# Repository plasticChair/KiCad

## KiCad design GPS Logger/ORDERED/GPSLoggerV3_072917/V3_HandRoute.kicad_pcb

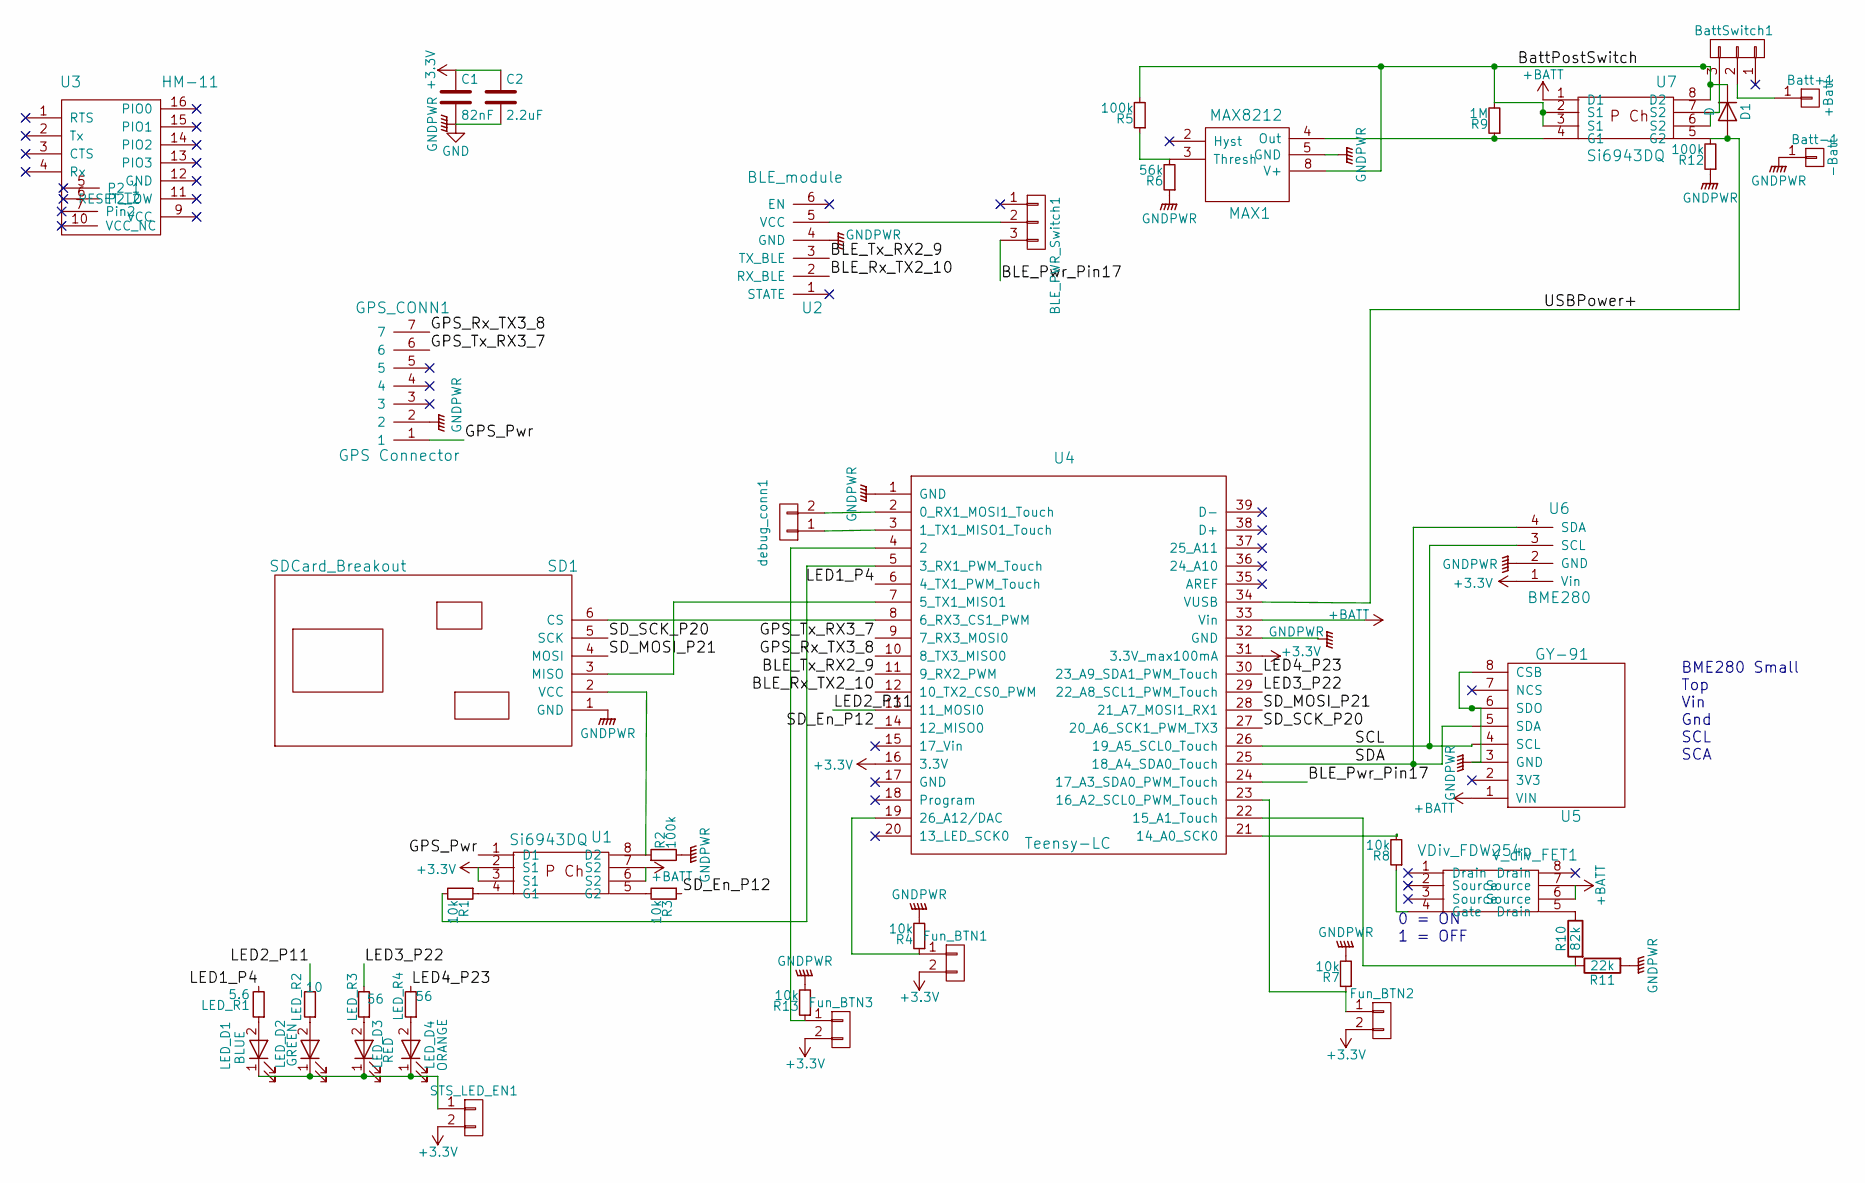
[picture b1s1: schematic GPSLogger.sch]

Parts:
BLE_PWR_Switch1: BLE_PWR_Switch; Pin_Header_1x03_Pitch2.54mm
Batt+1: +Batt; Pin_Header_1x01_Pitch2.54mm
Batt-1: -Batt; Pin_Header_1x01_Pitch2.54mm
BattSwitch1: BattSwitch; Pin_Header_1x03_Pitch2.54mm
C1: 82nF; C_0805_HandSoldering
C2: 2.2uF; C_0805_HandSoldering
D1: D; D_SOD-323
Fun_BTN1, Fun_BTN3: LVCutoff_reset; SMD_Switch_3x6
Fun_BTN2: Fun_BTN; SMD_Switch_3x6
GPS_CONN1: GPS Connector; Pin_Header_Angled_1x07_Pitch2.54mm
LED_D1: BLUE; LED_0805
LED_D2: GREEN; LED_0805
LED_D3: RED; LED_0805
LED_D4: ORANGE; LED_0805
LED_R1: 5.6; R_0805_HandSoldering
LED_R2: 10; R_0805_HandSoldering
LED_R3, LED_R4: 56; R_0805_HandSoldering
MAX1: MAX8212; SOIC-8-N
R1, R3, R4, R7, R8, R13: 10k; R_0805_HandSoldering
R2, R5, R12: 100k; R_0805_HandSoldering
R6: 56k; R_0805_HandSoldering
R9: 1M; R_0805_HandSoldering
R10: 82k; R_0805_HandSoldering
R11: 22k; R_0805_HandSoldering
SD1: SDCard_Breakout
STS_LED_EN1: STS_LED_EN; SMD_Switch_3x6
U1, U7: Si6943DQ; TSSOP-8_4.4x3mm_Pitch0.65mm_custom
U2: BLE_module; HM-10_breakout
U3: HM-11; HM-11_Breakout
U4: Teensy-LC; Teensy_LC
U5: GY-91
U6: BME280; BME280_tiny
V_div_FET1: VDiv_FDW254p; TSSOP-8_4.4x3mm_Pitch0.65mm_custom
debug_conn1: debug_conn; Pin_Header_Angled_1x02_Pitch2.54mm

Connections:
+3V3: C1.1, C2.1, Fun_BTN1.2, Fun_BTN2.2, Fun_BTN3.2, STS_LED_EN1.2, U1.2 (S1), U1.3 (S1), U4.16 (3.3V), U4.31 (3.3V_max100mA), U6.1 (Vin)
+BATT: U1.6 (S2), U1.7 (S2), U4.33 (Vin), U5.1 (VIN), U7.1 (D1), V_div_FET1.6 (Source), V_div_FET1.7 (Source)
/BLE_Pwr_Pin17: BLE_PWR_Switch1.3, U4.24 (17_A3_SDA0_PWM_Touch)
/BLE_Rx_TX2_10: U2.2 (RX_BLE), U4.12 (10_TX2_CS0_PWM)
/BLE_Tx_RX2_9: U2.3 (TX_BLE), U4.11 (9_RX2_PWM)
/BattPostSwitch: D1.1 (K), MAX1.8 (V+), R5.2, R9.2, U7.2 (S1), U7.3 (S1), U7.8 (D2)
/GPS_Pwr: GPS_CONN1.1, U1.1 (D1)
/GPS_Rx_TX3_8: GPS_CONN1.7, U4.10 (8_TX3_MISO0)
/GPS_Tx_RX3_7: GPS_CONN1.6, U4.9 (7_RX3_MOSI0)
/LED1_P4: LED_R1.2, U4.6 (4_TX1_PWM_Touch)
/LED2_P11: LED_R2.2, U4.13 (11_MOSI0)
/LED3_P22: LED_R3.2, U4.29 (22_A8_SCL1_PWM_Touch)
/LED4_P23: LED_R4.2, U4.30 (23_A9_SDA1_PWM_Touch)
/SCL: U4.26 (19_A5_SCL0_Touch), U5.4 (SCL), U6.3 (SCL)
/SDA: U4.25 (18_A4_SDA0_Touch), U5.5 (SDA), U6.4 (SDA)
/SD_En_P12: R3.1, U4.14 (12_MISO0)
/SD_MOSI_P21: SD1.4 (MOSI), U4.28 (21_A7_MOSI1_RX1)
/SD_SCK_P20: SD1.5 (SCK), U4.27 (20_A6_SCK1_PWM_TX3)
/USBPower+: D1.2 (A), R12.2, U4.34 (VUSB), U7.5 (G2)
GND: Batt-1.1, C1.2, C2.2, GPS_CONN1.2, MAX1.5 (GND), R2.2, R4.2, R6.1, R7.2, R11.2, R12.1, R13.2, SD1.1 (GND), U2.4 (GND), U4.1 (GND), U4.32 (GND), U5.3 (GND), U5.6 (SDO), U5.8 (CSB), U6.2 (GND)
unnamed: BLE_PWR_Switch1.2, U2.5 (VCC)
unnamed: Batt+1.1, BattSwitch1.2
unnamed: BattSwitch1.3, U7.6 (S2), U7.7 (S2)
unnamed: Fun_BTN1.1, R4.1, U4.19 (26_A12/DAC)
unnamed: Fun_BTN2.1, R7.1, U4.23 (16_A2_SCL0_PWM_Touch)
unnamed: Fun_BTN3.1, R13.1, U4.4 (2)
unnamed: LED_D1.1 (K), LED_D2.1 (K), LED_D3.1 (K), LED_D4.1 (K), STS_LED_EN1.1
unnamed: LED_D1.2 (A), LED_R1.1
unnamed: LED_D2.2 (A), LED_R2.1
unnamed: LED_D3.2 (A), LED_R3.1
unnamed: LED_D4.2 (A), LED_R4.1
unnamed: MAX1.3 (Thresh), R5.1, R6.2
unnamed: MAX1.4 (Out), R9.1, U7.4 (G1)
unnamed: R1.1, U1.4 (G1)
unnamed: R1.2, U4.5 (3_RX1_PWM_Touch)
unnamed: R2.1, SD1.2 (VCC), U1.8 (D2)
unnamed: R3.2, U1.5 (G2)
unnamed: R8.1, V_div_FET1.4 (Gate)
unnamed: R8.2, U4.21 (14_A0_SCK0)
unnamed: R10.1, V_div_FET1.5 (Drain)
unnamed: R10.2, R11.1, U4.22 (15_A1_Touch)
unnamed: SD1.3 (MISO), U4.7 (5_TX1_MISO1)
unnamed: SD1.6 (CS), U4.8 (6_RX3_CS1_PWM)
unnamed: U4.2 (0_RX1_MOSI1_Touch), debug_conn1.2
unnamed: U4.3 (1_TX1_MISO1_Touch), debug_conn1.1

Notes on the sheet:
0 = ON 1 = OFF
BME280 Small Top Vin Gnd SCL SCA

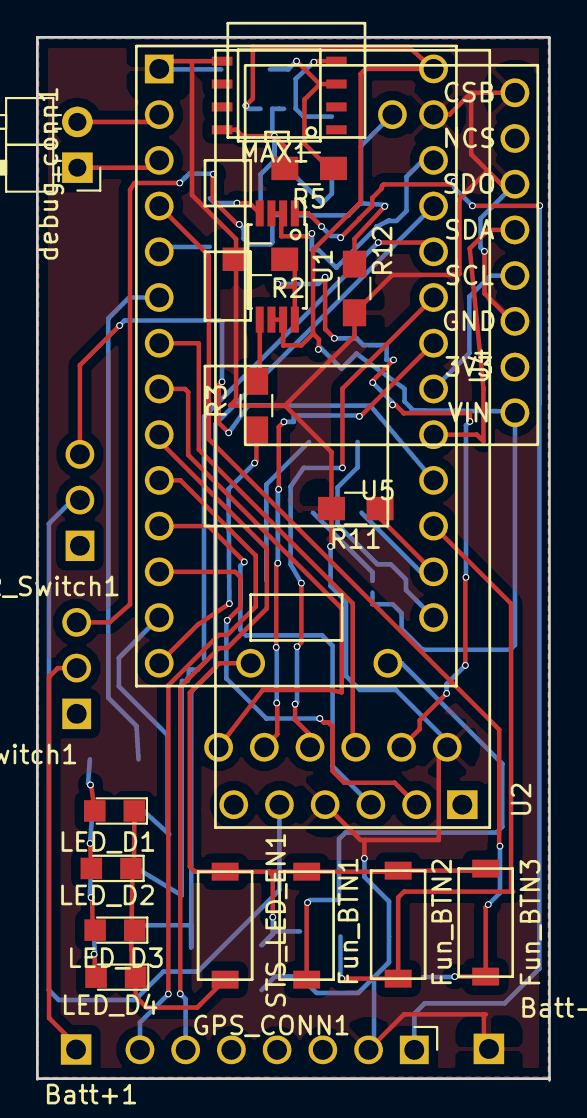
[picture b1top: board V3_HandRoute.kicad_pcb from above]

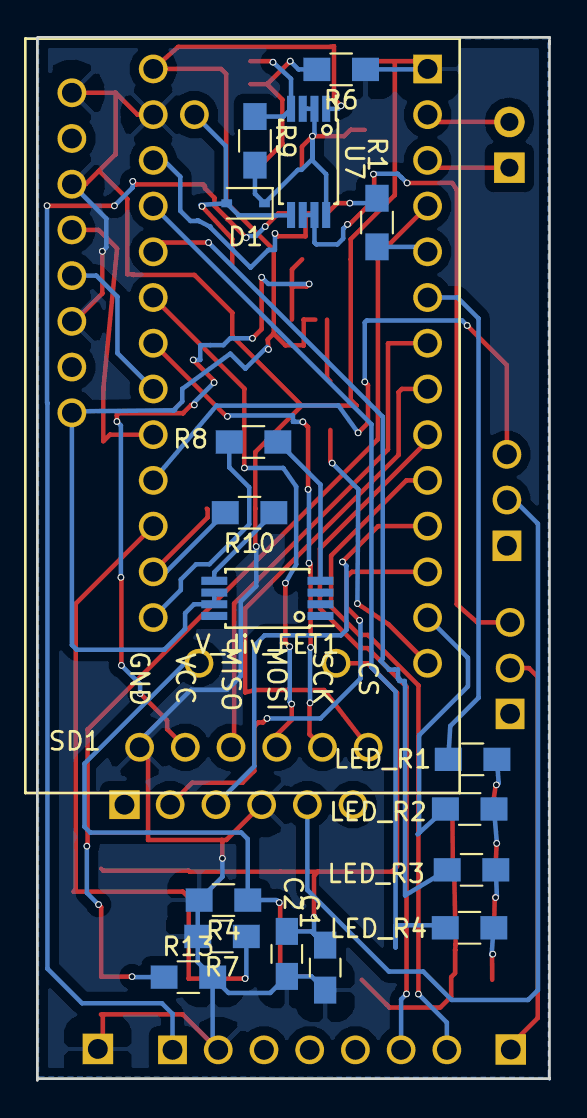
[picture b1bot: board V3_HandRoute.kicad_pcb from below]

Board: 2 copper layers, 28.4 x 58.0 mm, 42 parts (18 on the bottom side), 45 nets.

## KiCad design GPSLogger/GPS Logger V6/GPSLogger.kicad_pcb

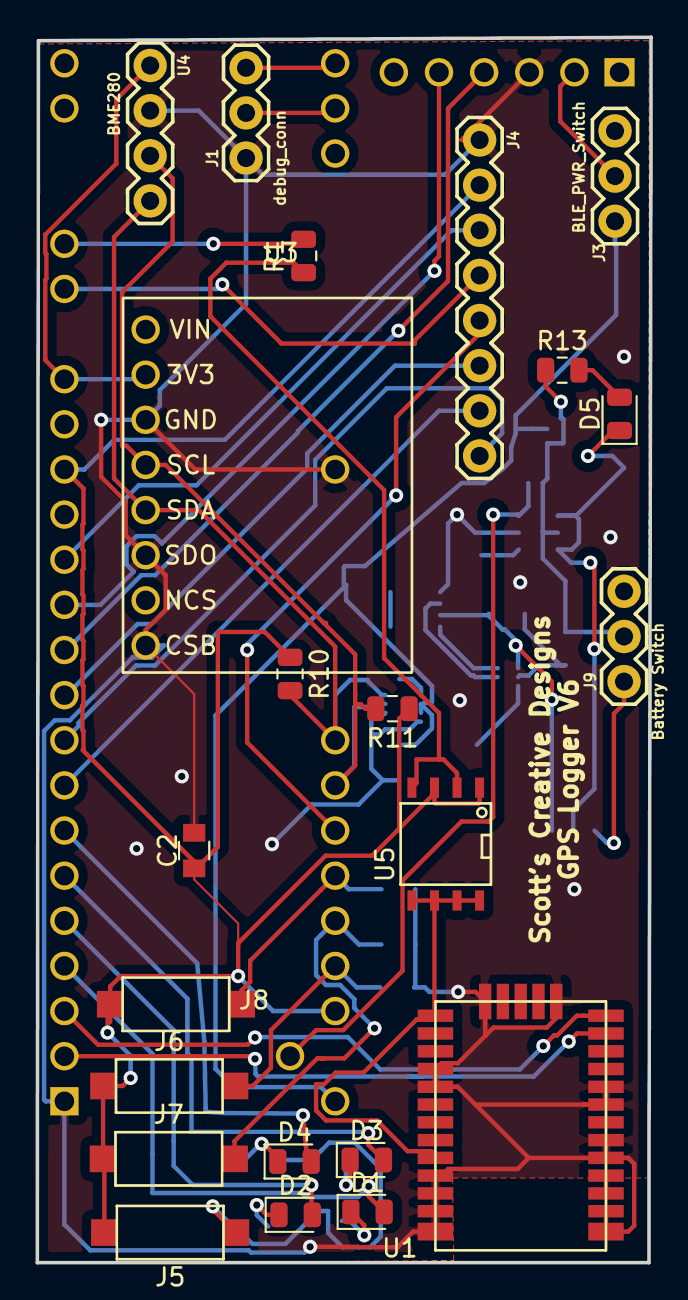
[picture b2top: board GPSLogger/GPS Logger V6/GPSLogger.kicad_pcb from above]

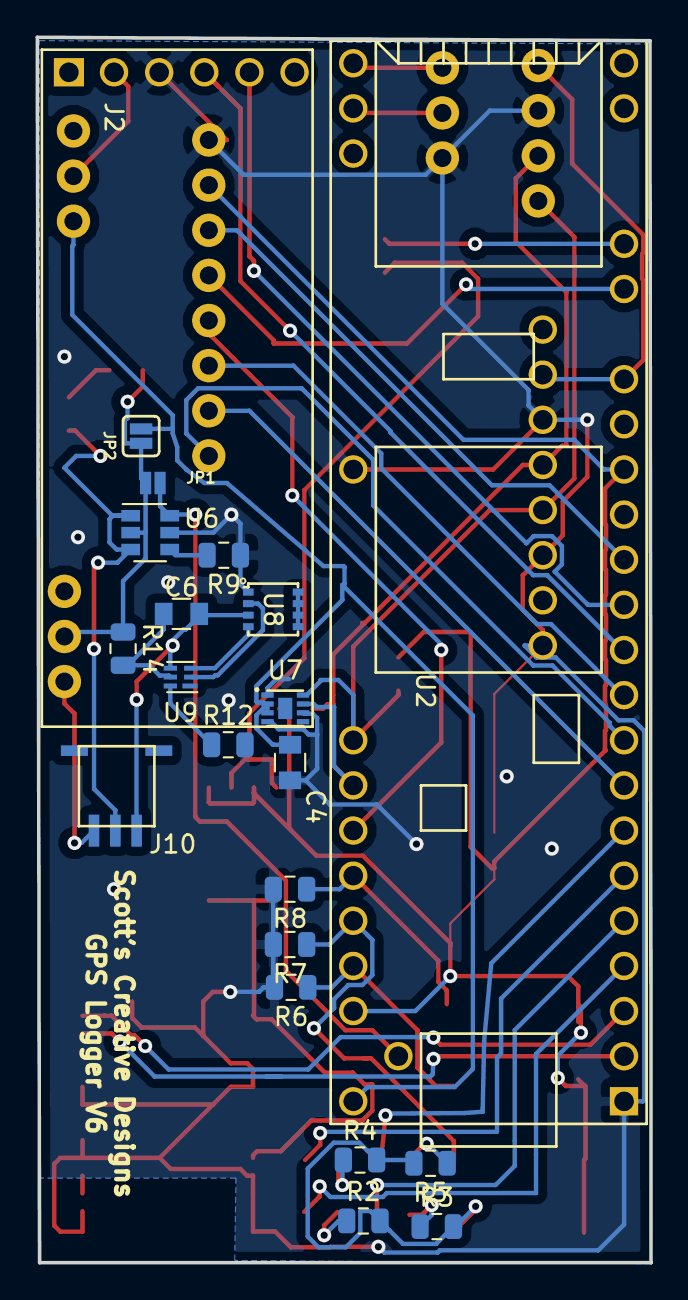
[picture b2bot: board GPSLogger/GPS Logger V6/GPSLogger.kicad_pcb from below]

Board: 2 copper layers, 34.5 x 69.0 mm, 43 parts (21 on the bottom side), 47 nets.

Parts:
C2: 2.2u; C_0805
C4: 1u; C_0805
C6: 0.1u; C_0805
D1: LED_B; LED_0805_2012Metric
D2: LED_G; LED_0805_2012Metric
D3: LED_R; LED_0805_2012Metric
D4: LED_O; LED_0805_2012Metric
D5: LED; LED_0805_2012Metric
J1: debug_conn; 1X03
J2: BLE_Module; HM-10_breakout
J3: BLE_PWR_Switch; 1X03
J4: Conn_01x08_Male; 1X08
J5: LED_BUTTON; Tact_SMD_Switch
J6: BTN1; Tact_SMD_Switch
J7: BTN2; Tact_SMD_Switch
J8: BTN3; Tact_SMD_Switch
J9: Battery Switch; 1X03
J10: Batt_Connector; molex_78172-0003
JP1: Jumper_NO_Small; SMT-JUMPER_2_NO_NO-SILK
JP2: Jumper_NC_Small; SMT-JUMPER_2_NC_PASTE_SILK
R1, R6, R7, R8: 10k; R_0805_2012Metric
R2: 5.6; R_0805_2012Metric
R3: 10; R_0805_2012Metric
R4, R5: 56; R_0805_2012Metric
R9: 1k; R_0805_2012Metric
R10, R11: R; R_0805_2012Metric
R12: 2.2k; R_0805_2012Metric
R13, R14: 330; R_0805_2012Metric
U1: CAM_M8Q; CAM-M8Q
U2: Teensy3.6; Teensy35_36
U3: GY-91
U4: BME280; 1X04
U5: APM4953; SOIC-8-N
U6: BQ21040; SOT-23-6
U7: MAX17048; TQFN-8_2x2x0.75
U8: ECH8693R; sot-28
U9: BQ297xy; WSON-6_1.5x1.5mm_P0.5mm

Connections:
+3V3: C2.1, J4.2, J5.1, J6.2, J7.2, J8.2, R10.1, R11.1, U2.15, U2.51, U5.1, U5.3
/BLE_Pwr: J2.2, J3.2
/BLE_Rx_TX2_P10: J2.5, U2.12
/BLE_Tx_RX2_P9: J2.4, U2.11
/BatteryManagement/NTC: D5.1, J10.2, U6.1, U6.3
/Debug_Rx_TX5_P33: J1.3, U2.30
/Debug_Tx_RX5_P34: J1.2, U2.31
/GPS_Rx_TX1_P1: U1.26, U2.3
/GPS_Tx_RX1_P0: U1.25, U2.2
/Screen_BUSY_P7: J4.8, U2.9
/Screen_CS_P20: J4.5, U2.47
/Screen_DC_P8: J4.6, U2.10
/Screen_DIN_P11: J4.3, U2.13
/Screen_RST_P6: J4.7, U2.8
/Screen_SCK_P27: J4.4, U2.19
/Sensor_PWR_P25: U2.17, U3.2, U4.1
BattPwr: C4.1, J3.1, JP2.1, U2.53, U7.2, U7.3
BattRtn: C2.2, C4.2, J1.1, J2.3, J4.1, R6.2, R7.2, R8.2, R9.1, R12.2, U1.4, U1.5, U1.10, U1.11, U1.12, U1.13, U1.14, U1.15, U1.18, U1.19, U1.21, U1.22, U1.27, U1.31, U2.1, U2.39, U3.3, U3.6, U3.8, U4.2, U6.5, U7.1, U7.4, U7.6, U8.1
Fun_Btn_1_P23: J6.1, R6.1, U2.50
Fun_Btn_2_P22: J7.1, R7.1, U2.49
Fun_Btn_3_P21: J8.1, R8.1, U2.48
GPS_Pwr: U1.1, U1.9, U5.5, U5.6, U5.7, U5.8
GPS_Pwr_En_P28: R1.2, U2.20
LED1_P2: D1.2, U2.4
LED2_P3: D2.2, U2.5
LED3_P4: D3.2, U2.6
LED4_P5: D4.2, U2.7
unnamed: C6.1, R14.2, U9.5
unnamed: C6.2, J10.1, U8.3, U9.4
unnamed: D1.1, R2.1
unnamed: D2.1, R3.1
unnamed: D3.1, R4.1
unnamed: D4.1, R5.1
unnamed: D5.2, R13.2
unnamed: J5.2, R2.2, R3.2, R4.2, R5.2
unnamed: J9.2, JP1.2, JP2.2, R13.1, R14.1, U6.2
unnamed: J9.1, J10.3
unnamed: R1.1, U5.2, U5.4
unnamed: R9.2, U6.4
unnamed: R12.1, U9.6
unnamed: U1.16, U1.17
unnamed: U8.2, U9.2
unnamed: U8.4, U9.3
unnamed: U8.5, U8.6, U8.7, U8.8
SCL: R11.2, U2.46, U3.4, U4.3, U7.7
SDA: R10.2, U2.45, U3.5, U4.4, U7.8
USBPwr: JP1.1, U2.54, U6.6

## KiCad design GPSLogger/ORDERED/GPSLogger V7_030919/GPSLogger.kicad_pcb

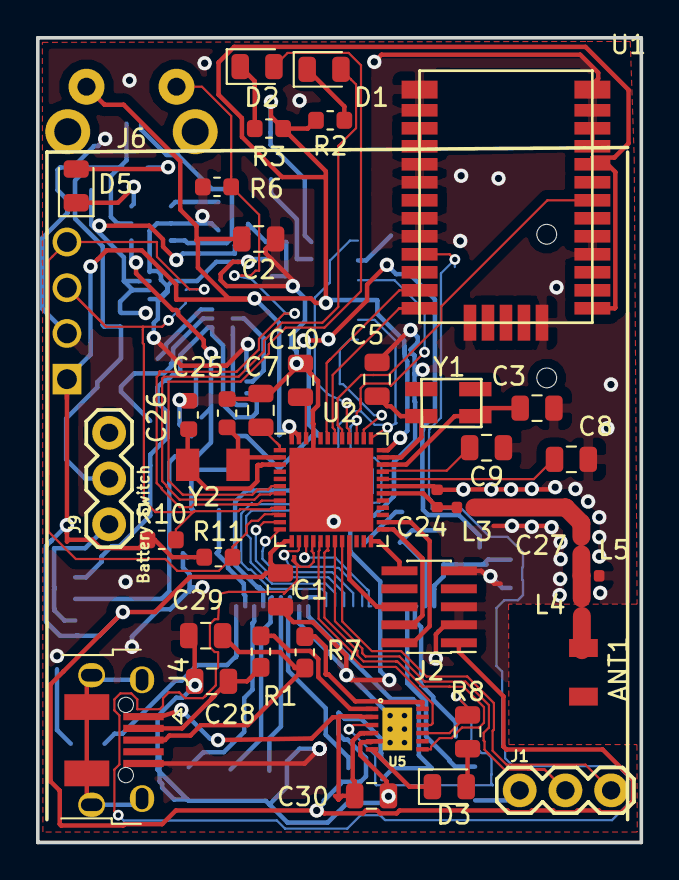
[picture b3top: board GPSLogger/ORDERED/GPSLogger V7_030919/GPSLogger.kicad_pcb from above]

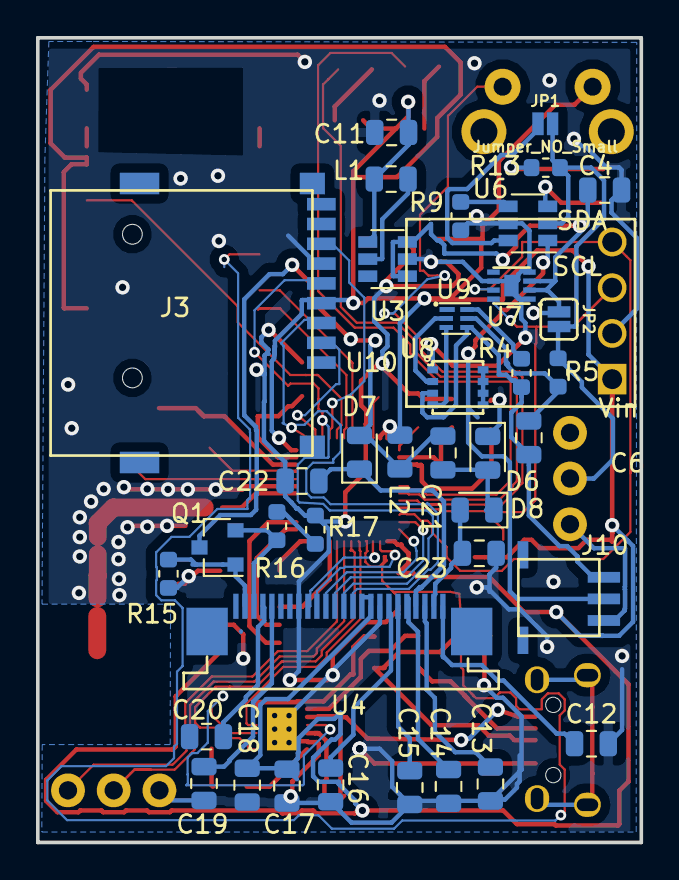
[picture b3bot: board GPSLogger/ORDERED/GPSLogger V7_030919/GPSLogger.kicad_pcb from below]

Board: 2 copper layers, 33.5 x 44.7 mm, 80 parts (39 on the bottom side), 79 nets.

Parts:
ANT1: 2450AT18A100E
C1, C7, C8, C9, C10, C12, C13, C14, C15, C16, C17, C18, C19, C20, C21, C22, C23: 82n; C_0805_2012Metric
C2: 2.2u; C_0805_2012Metric
C3, C5, C11: C; C_0805_2012Metric
C4: 1u; C_0805_2012Metric
C6: 0.1u; C_0805_2012Metric
C24, C27: C; C_0402_1005Metric
C25, C26: C; C_0603_1608Metric
C28, C29: 47pF; C_0805_2012Metric
C30: 100nF; C_0805_2012Metric
D1: LED_B; LED_0805_2012Metric
D2: LED_G; LED_0805_2012Metric
D3: TXLED; LED_0805_2012Metric
D5: LED; LED_0805_2012Metric
D6, D7, D8: D_Schottky; D_0805_2012Metric
J1: debug_conn; 1X03
J2: Conn_02x05_Odd_Even; PinHeader_2x05_P1.00mm_Vertical_SMD
J3: Micro_SD_Card; microSD_ebay
J4: USB_B_Micro; USB_Micro-B_Adafruit
J6: BTN1; ebay_RA_Mom_switch
J9: Battery Switch; 1X03
J10: Batt_Connector; molex_78172-0003
JP1: Jumper_NO_Small; SMT-JUMPER_2_NO_NO-SILK
JP2: Jumper_NC_Small; SMT-JUMPER_2_NC_PASTE_SILK
L1, L2: INDUCTOR; L_0805_2012Metric
L3, L4, L5: INDUCTOR; L_0402_1005Metric
Q1: Q_NMOS_GSD; SOT-23
R1, R7: 27R; R_0603_1608Metric_Pad1.05x0.95mm_HandSolder
R2: 5.6; R_0603_1608Metric
R3: 10; R_0603_1608Metric
R4: 2.2k; R_0603_1608Metric
R5, R13: 330; R_0603_1608Metric
R6: 10k; R_0603_1608Metric
R8: 270R; R_0805_2012Metric
R9: 1k; R_0603_1608Metric
R10, R11: R; R_0603_1608Metric
R15, R16, R17: R_US; R_0603_1608Metric
U1: CAM_M8Q; CAM-M8Q
U2: nRF52832-QFxx; QFN-48-1EP_6x6mm_P0.4mm_EP4.66x4.66mm
U3: LM3671; SOT-23-6
U4: 24pin_Flex_bottom
U5: FT234XD; DFN-12
U6: BQ21040; SOT-23-6
U7: MAX17048; TQFN-8_2x2x0.75
U8: ECH8693R; sot-28
U9: BQ297xy; WSON-6_1.5x1.5mm_P0.5mm
U10: BME280-EbayParts; BME280_tiny
Y1: Crystal; ECS-320-12-33Q
Y2: Crystal; TFE322P32K7680R

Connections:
/BatteryManagement/Batt-: C6.2, J10.1, R4.2, U8.3, U9.4
/BatteryManagement/NTC: J10.2, U6.1
/Button and LEDs/FTDI_3V3: R8.2, U5.3, U5.9
/DEC1: C7.1, U2.1
/DEC2: C8.1, U2.32
/DEC3: C9.1, U2.33
/DEC4: C10.1, U2.46
/Debug_Rx: J1.2, U2.19
/Debug_Tx: J1.3, U2.20
/EINK/EINK_GDR: Q1.1, R15.1, U4.2
/EINK/EINK_PREVGH: C22.1, D7.1, U4.21
/EINK/EINK_PREVGL: C23.2, D8.2, U4.23
/EINK/EINK_RESE: Q1.2, R16.1, U4.3
/EINK/EINK_VGH: C19.1, U4.5
/EINK/EINK_VGL: C20.1, U4.4
/EINK_BUSY: U2.15, U4.9
/EINK_DC: U2.12, U4.11
/EINK_RST: U2.14, U4.10
/GPS_ExtInt: U1.7, U2.41
/GPS_Reset: U1.23, U2.16
/GPS_Rx: U1.26, U2.42
/GPS_Tx: U1.25, U2.43
/RESET: J2.10, U2.24
/SPI_CLK: J3.5, U2.39, U4.13
/SPI_CS: J3.2, U2.38
/SPI_EINK_CS: U2.11, U4.12
/SPI_MISO: J3.7, U2.40
/SPI_MOSI: J3.3, U2.37, U4.14
/SWDCLK: J2.4, U2.25
/SWDIO: J2.2, U2.26
/SWO: J2.6, U2.21
BattPwr: C4.1, JP2.1, U3.1, U3.3, U7.2, U7.3
BattRtn: C1.2, C2.2, C3.1, C4.2, C5.1, C7.2, C8.2, C9.2, C10.2, C11.2, C12.2, C13.2, C14.2, C15.2, C16.2, C17.2, C18.2, C19.2, C20.2, C22.2, C23.1, C24.2, C25.2, C26.2, C28.2, C29.2, C30.1, D6.1, J1.1, J2.3, J2.5, J2.9, J3.6, J4.5, L5.1, R6.2, R9.1, R15.2, R17.2, U1.4, U1.5, U1.10, U1.11, U1.12, U1.13, U1.14, U1.15, U1.18, U1.19, U1.21, U1.22, U1.27, U1.31, U2.31, U2.45, U2.49, U3.2, U4.8, U4.17, U5.5, U5.13, U6.5, U7.1, U7.4, U7.6, U7.9, U8.1, U10.2
Fun_Btn_1_P23: J6.1, R6.1, U2.8
LED1_P2: D1.2, U2.7
LED2_P3: D2.2, U2.6
unnamed: ANT1.1, L4.1
unnamed: C3.2, U2.34, Y1.1
unnamed: C5.2, U2.35, Y1.2
unnamed: C6.1, R5.2, U9.5
unnamed: C12.1, U4.24
unnamed: C13.1, U4.22
unnamed: C14.1, U4.20
unnamed: C15.1, U4.19
unnamed: C16.1, U4.18
unnamed: C21.1, D7.2, L2.1, Q1.3
unnamed: C21.2, D6.2, D8.1
unnamed: C24.1, L3.2, U2.30
unnamed: C25.1, U2.2, Y2.1
unnamed: C26.1, U2.3, Y2.2
unnamed: C27.1, L3.1
unnamed: C27.2, L4.2, L5.2
unnamed: C28.1, J4.2, R1.2
unnamed: C29.1, J4.3, R7.2
unnamed: D1.1, R2.1
unnamed: D2.1, R3.1
unnamed: D3.1, U5.6
unnamed: D3.2, R8.1
unnamed: D5.1, U6.3
unnamed: D5.2, R13.2
unnamed: J9.2, JP1.2, JP2.2, R5.1, R13.1, U6.2
unnamed: J9.1, J10.3
unnamed: L1.1, U3.5
unnamed: R1.1, U5.1
unnamed: R4.1, U9.6
unnamed: R7.1, U5.12
unnamed: R9.2, U6.4
unnamed: R16.2, R17.1
unnamed: U1.16, U1.17
unnamed: U8.2, U9.2
unnamed: U8.4, U9.3
unnamed: U8.5, U8.6, U8.7, U8.8
SCL: R11.2, U2.10, U7.7, U10.4
SDA: R10.2, U2.9, U7.8, U10.3
UART_RX: U2.17, U5.10
UART_TX: U2.18, U5.7
USBPwr: JP1.1, U6.6
USB_PWR: C30.2, J4.1, U5.2, U5.4
Vdd: C1.1, C2.1, C11.1, C17.1, C18.1, J2.1, J3.4, J6.2, L1.2, L2.2, R2.2, R3.2, R10.1, R11.1, U1.1, U1.9, U2.13, U2.36, U2.47, U2.48, U3.4, U4.15, U4.16, U10.1

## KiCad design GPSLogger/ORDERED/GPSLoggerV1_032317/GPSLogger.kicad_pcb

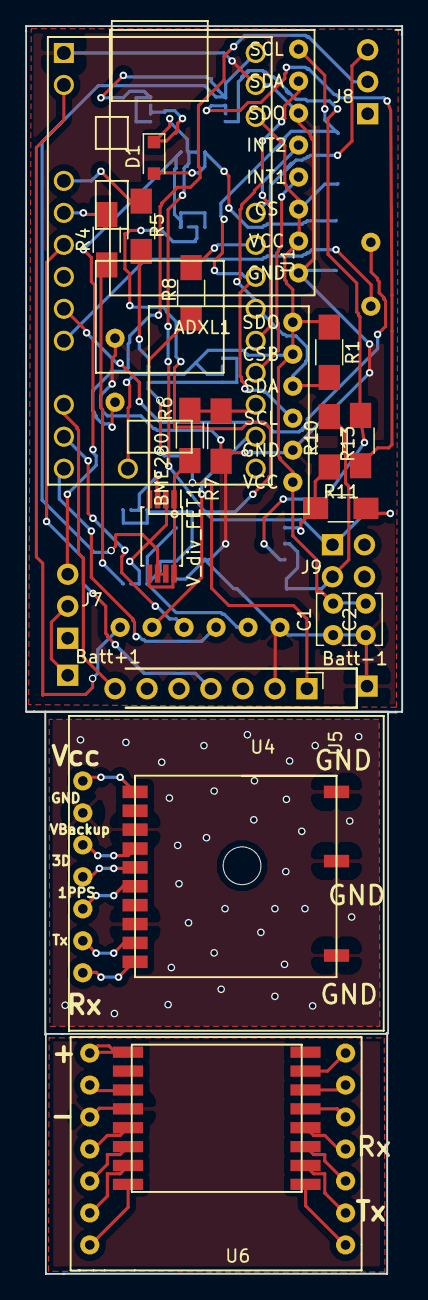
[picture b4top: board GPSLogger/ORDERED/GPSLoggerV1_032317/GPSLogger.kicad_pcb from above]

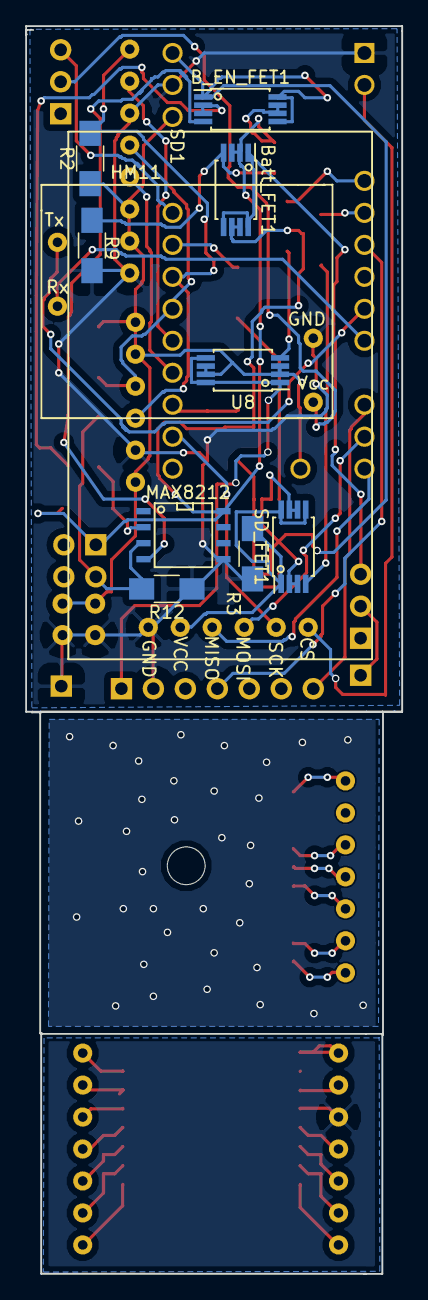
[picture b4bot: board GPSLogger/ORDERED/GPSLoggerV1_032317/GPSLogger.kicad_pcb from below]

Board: 2 copper layers, 29.9 x 99.1 mm, 35 parts (11 on the bottom side), 36 nets.

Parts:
ADXL1: ADXL345_Breakout
BME280: BME280_Breakout
B_EN_FET1: Batt_En_FET; TSSOP-8_4.4x3mm_Pitch0.65mm_custom
Batt+1: +Batt; Pin_Header_1x01_Pitch2.54mm
Batt-1: -Batt; Pin_Header_1x01_Pitch2.54mm
Batt_FET1: Batt_EnFDW254p; TSSOP-8_4.4x3mm_Pitch0.65mm_custom
C1, C2: C; C_Rect_L4.0mm_W2.5mm_P2.50mm
D1: D_Schottky; D_SOD-323_HandSoldering
HM11: HM-11_BreakConns
J7: BattSwitch; Pin_Header_1x03_Pitch2.54mm
J8: HM11Switch; Pin_Header_1x03_Pitch2.54mm
J9: CONN_02X02; Pin_Header_Angled_2x02_Pitch2.54mm
MAX8212: MAX8212; SOIC-8-N
R1, R2, R6, R7: R; R_1206_HandSoldering
R3, R4, R5: R_Small; R_1206_HandSoldering
R8: 10k; R_1206_HandSoldering
R9: 100k; R_1206_HandSoldering
R10, R11, R12, R13: 1M; R_1206_HandSoldering
SD1: SDCard_Breakout
SD_FET1: SD_EN_FDW254p; TSSOP-8_4.4x3mm_Pitch0.65mm_custom
U1: Teensy-LC; Teensy_LC
U4: GNS601_Breakout
U5: GPS Connector; Pin_Header_Angled_1x07_Pitch2.54mm
U6: HM-11; HM-11_Breakout
U8: GPS_FDW254p; TSSOP-8_4.4x3mm_Pitch0.65mm_custom
V_div_FET1: VDiv_FDW254p; TSSOP-8_4.4x3mm_Pitch0.65mm_custom

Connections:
+3V3: ADXL1.2, ADXL1.3, BME280.1, BME280.2, BME280.6, C1.1, C2.1, R1.1, R2.1, U1.16, U1.31, U8.2, U8.3, U8.6, U8.7
+BATT: B_EN_FET1.1, B_EN_FET1.5, B_EN_FET1.8, SD_FET1.2, SD_FET1.3, SD_FET1.6, SD_FET1.7, U1.33, V_div_FET1.2, V_div_FET1.3, V_div_FET1.6, V_div_FET1.7
GND: ADXL1.1, ADXL1.6, BME280.5, Batt-1.1, C1.2, C2.2, HM11.12, MAX8212.5, R3.2, R7.2, R9.1, R12.1, SD1.1, U1.1, U5.2
unnamed: ADXL1.4, U1.23
unnamed: ADXL1.5, U1.24
unnamed: ADXL1.7, BME280.3, R1.2, U1.25
unnamed: ADXL1.8, BME280.4, R2.2, U1.26
unnamed: B_EN_FET1.2, B_EN_FET1.3, R13.2
unnamed: B_EN_FET1.4, MAX8212.4, R13.1
unnamed: B_EN_FET1.6, B_EN_FET1.7, Batt_FET1.2, Batt_FET1.3, Batt_FET1.6, Batt_FET1.7, D1.1, J9.1, MAX8212.8, R11.2
unnamed: Batt+1.1, J7.2
unnamed: Batt_FET1.1, Batt_FET1.5, Batt_FET1.8, J7.3
unnamed: Batt_FET1.4, D1.2, R9.2
unnamed: HM11.2, U1.9
unnamed: HM11.4, U1.10
unnamed: HM11.9, J8.2
unnamed: J8.3, U1.28
unnamed: J9.3, MAX8212.3, R10.1, R12.2
unnamed: MAX8212.2, R10.2, R11.1
unnamed: R3.1, SD1.2, SD_FET1.1, SD_FET1.5, SD_FET1.8
unnamed: R4.1, SD_FET1.4
unnamed: R4.2, U1.6
unnamed: R5.1, U8.4
unnamed: R5.2, U1.5
unnamed: R6.1, R7.1, U1.22
unnamed: R6.2, V_div_FET1.1, V_div_FET1.5, V_div_FET1.8
unnamed: R8.1, V_div_FET1.4
unnamed: R8.2, U1.27
unnamed: SD1.3, U1.14
unnamed: SD1.4, U1.13
unnamed: SD1.5, U1.21
unnamed: SD1.6, U1.2
unnamed: U1.7, U5.4
unnamed: U1.12, U5.7
unnamed: U4.3, U4.8, U4.11, U4.12, U4.13
unnamed: U5.1, U8.1, U8.5, U8.8

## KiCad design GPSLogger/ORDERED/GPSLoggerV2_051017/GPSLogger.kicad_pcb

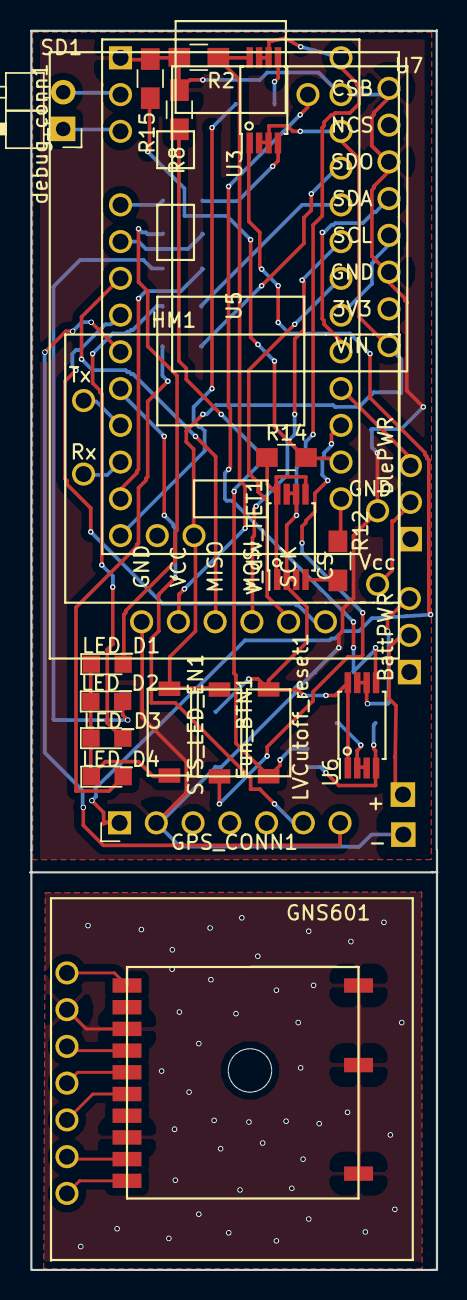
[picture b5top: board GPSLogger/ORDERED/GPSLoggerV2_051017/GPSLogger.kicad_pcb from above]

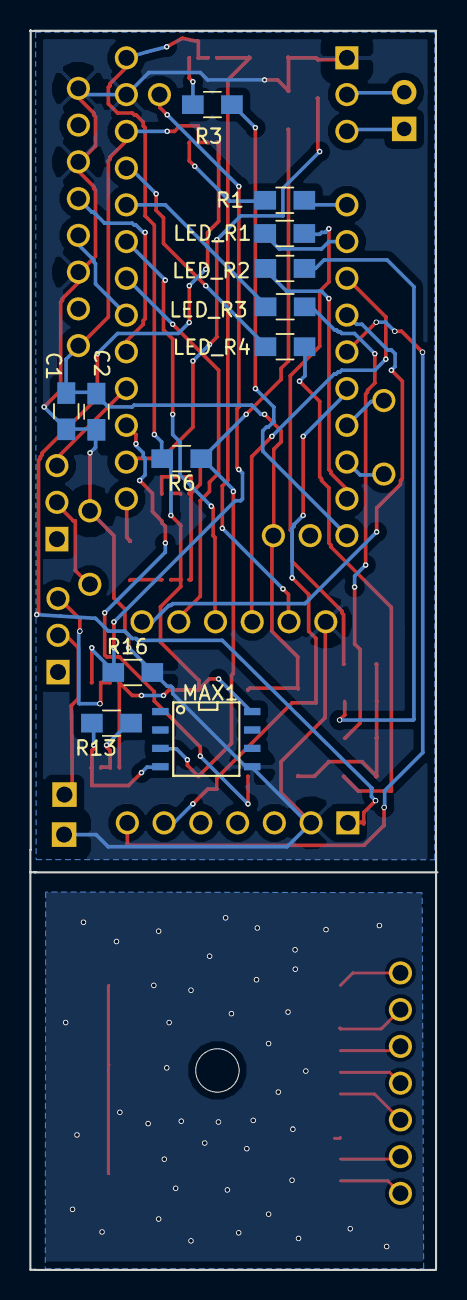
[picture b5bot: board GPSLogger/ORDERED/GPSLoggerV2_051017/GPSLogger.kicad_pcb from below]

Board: 2 copper layers, 28.0 x 85.7 mm, 38 parts (12 on the bottom side), 44 nets.

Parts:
+: +Batt; Pin_Header_1x01_Pitch2.54mm
-: -Batt; Pin_Header_1x01_Pitch2.54mm
BattPWR: BattSwitch; Pin_Header_1x03_Pitch2.54mm
C1, C2: C; C_0805_HandSoldering
Fun_BTN1: Fun_BTN; SMD_Switch_3x6
GNS601: GNS601_Breakout
GPS_CONN1: GPS Connector; Pin_Header_Angled_1x07_Pitch2.54mm
HM1: HM-11_BreakConns
LED_D1, LED_D2, LED_D3, LED_D4: LED; LED_0805
LED_R1, LED_R2, LED_R3, LED_R4: XXk; R_0805_HandSoldering
LVCutoff_reset1: LVCutoff_reset; SMD_Switch_3x6
MAX1: MAX8212; SOIC-8-N
R1, R3, R12: 10k; R_0805_HandSoldering
R2, R6, R16: 100k; R_0805_HandSoldering
R8: 56k; R_0805_HandSoldering
R13: 1M; R_0805_HandSoldering
R14: 22k; R_0805_HandSoldering
R15: 68k; R_0805_HandSoldering
SD1: SDCard_Breakout
STS_LED_EN1: STS_LED_EN; SMD_Switch_3x6
U3, U6: Si6943DQ; TSSOP-8_4.4x3mm_Pitch0.65mm_custom
U5: Teensy-LC; Teensy_LC
U7: GY-91
V_div_FET1: VDiv_FDW254p; TSSOP-8_4.4x3mm_Pitch0.65mm_custom
blePWR: BLE_PWR_Switch; Pin_Header_1x03_Pitch2.54mm
debug_conn1: debug_conn; Pin_Header_Angled_1x02_Pitch2.54mm

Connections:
+3V3: C1.1, C2.1, Fun_BTN1.2, STS_LED_EN1.2, U3.2, U3.3, U5.16, U5.31, U7.1
+BATT: LVCutoff_reset1.1, MAX1.8, R6.2, U3.6, U3.7, U5.33, U6.1, U6.8, V_div_FET1.2, V_div_FET1.3, V_div_FET1.6, V_div_FET1.7
GND: -.1, C1.2, C2.2, GPS_CONN1.2, HM1.12, MAX1.5, R2.2, R8.1, R15.2, R16.1, SD1.1, U5.1, U5.32, U7.3, U7.6, U7.8
unnamed: HM1.9, blePWR.2
unnamed: U5.24, blePWR.3
unnamed: +.1, BattPWR.2
unnamed: BattPWR.3, U6.6, U6.7
unnamed: Fun_BTN1.1, U5.23
unnamed: GPS_CONN1.1, U3.1
unnamed: GPS_CONN1.6, U5.10
unnamed: GPS_CONN1.7, U5.9
unnamed: HM1.2, U5.11
unnamed: HM1.4, U5.12
unnamed: LED_D1.1, LED_D2.1, LED_D3.1, LED_D4.1, STS_LED_EN1.1
unnamed: LED_D1.2, LED_R1.1
unnamed: LED_D2.2, LED_R2.1
unnamed: LED_D3.2, LED_R3.1
unnamed: LED_D4.2, LED_R4.1
unnamed: LED_R1.2, U5.6
unnamed: LED_R2.2, U5.13
unnamed: LED_R3.2, U5.29
unnamed: LED_R4.2, U5.30
unnamed: LVCutoff_reset1.2, MAX1.3, R6.1, R8.2
unnamed: MAX1.4, R13.1, U6.4
unnamed: R1.1, U3.4
unnamed: R1.2, U5.5
unnamed: R2.1, SD1.2, U3.8
unnamed: R3.1, U5.14
unnamed: R3.2, U3.5
unnamed: R12.1, V_div_FET1.4
unnamed: R12.2, U5.21
unnamed: R13.2, U6.2, U6.3
unnamed: R14.1, V_div_FET1.1, V_div_FET1.5, V_div_FET1.8
unnamed: R14.2, R15.1, U5.22
unnamed: R16.2, U5.34, U6.5
unnamed: SD1.3, U5.7
unnamed: SD1.4, U5.28
unnamed: SD1.5, U5.27
unnamed: SD1.6, U5.8
unnamed: GNS601.3, GNS601.8, GNS601.11, GNS601.12, GNS601.13
unnamed: U5.2, debug_conn1.2
unnamed: U5.3, debug_conn1.1
unnamed: U5.25, U7.5
unnamed: U5.26, U7.4

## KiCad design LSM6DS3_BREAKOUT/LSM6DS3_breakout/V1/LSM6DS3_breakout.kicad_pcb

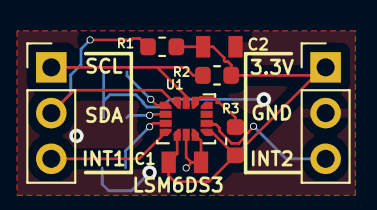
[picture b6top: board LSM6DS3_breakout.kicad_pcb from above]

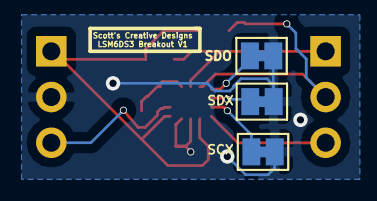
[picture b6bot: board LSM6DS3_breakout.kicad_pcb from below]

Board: 2 copper layers, 11 parts (3 on the bottom side), 10 nets.

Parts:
C1, C2: C_Small; 0805
J1, J2: Conn_01x03_Male; PinHeader_1x03_P2.54mm_Vertical
R1, R2: 5.1k; R_0603_1608Metric
R3: 10k; R_0603_1608Metric
SCX: J_NC; SolderJumper-2_P1.3mm_Bridged_Pad1.0x1.5mm
SDO: J_NC; SolderJumper-2_P1.3mm_Bridged_Pad1.0x1.5mm
SDX: J_NC; SolderJumper-2_P1.3mm_Bridged_Pad1.0x1.5mm
U1: LSM6DS3; LGA-14_3x2.5mm_P0.5mm_LayoutBorder3x4y

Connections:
+3V3: C1.2, C2.1, J2.1, R1.2, R2.2, R3.2, U1.5, U1.8
/CS: R3.1, U1.12
/INT1: J1.3, U1.4
/INT2: J2.3, U1.9
/SCL: J1.1, R2.1, U1.13
/SCX: SCX.1, U1.3
/SDA: J1.2, R1.1, U1.14
/SDO: SDO.1, U1.1
/SDX: SDX.1, U1.2
GND: C1.1, C2.2, J2.2, SCX.2, SDO.2, SDX.2, U1.6, U1.7

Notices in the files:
parts and their libraries:
Copyright 2016 Accelerated Designs. All rights reserved.
